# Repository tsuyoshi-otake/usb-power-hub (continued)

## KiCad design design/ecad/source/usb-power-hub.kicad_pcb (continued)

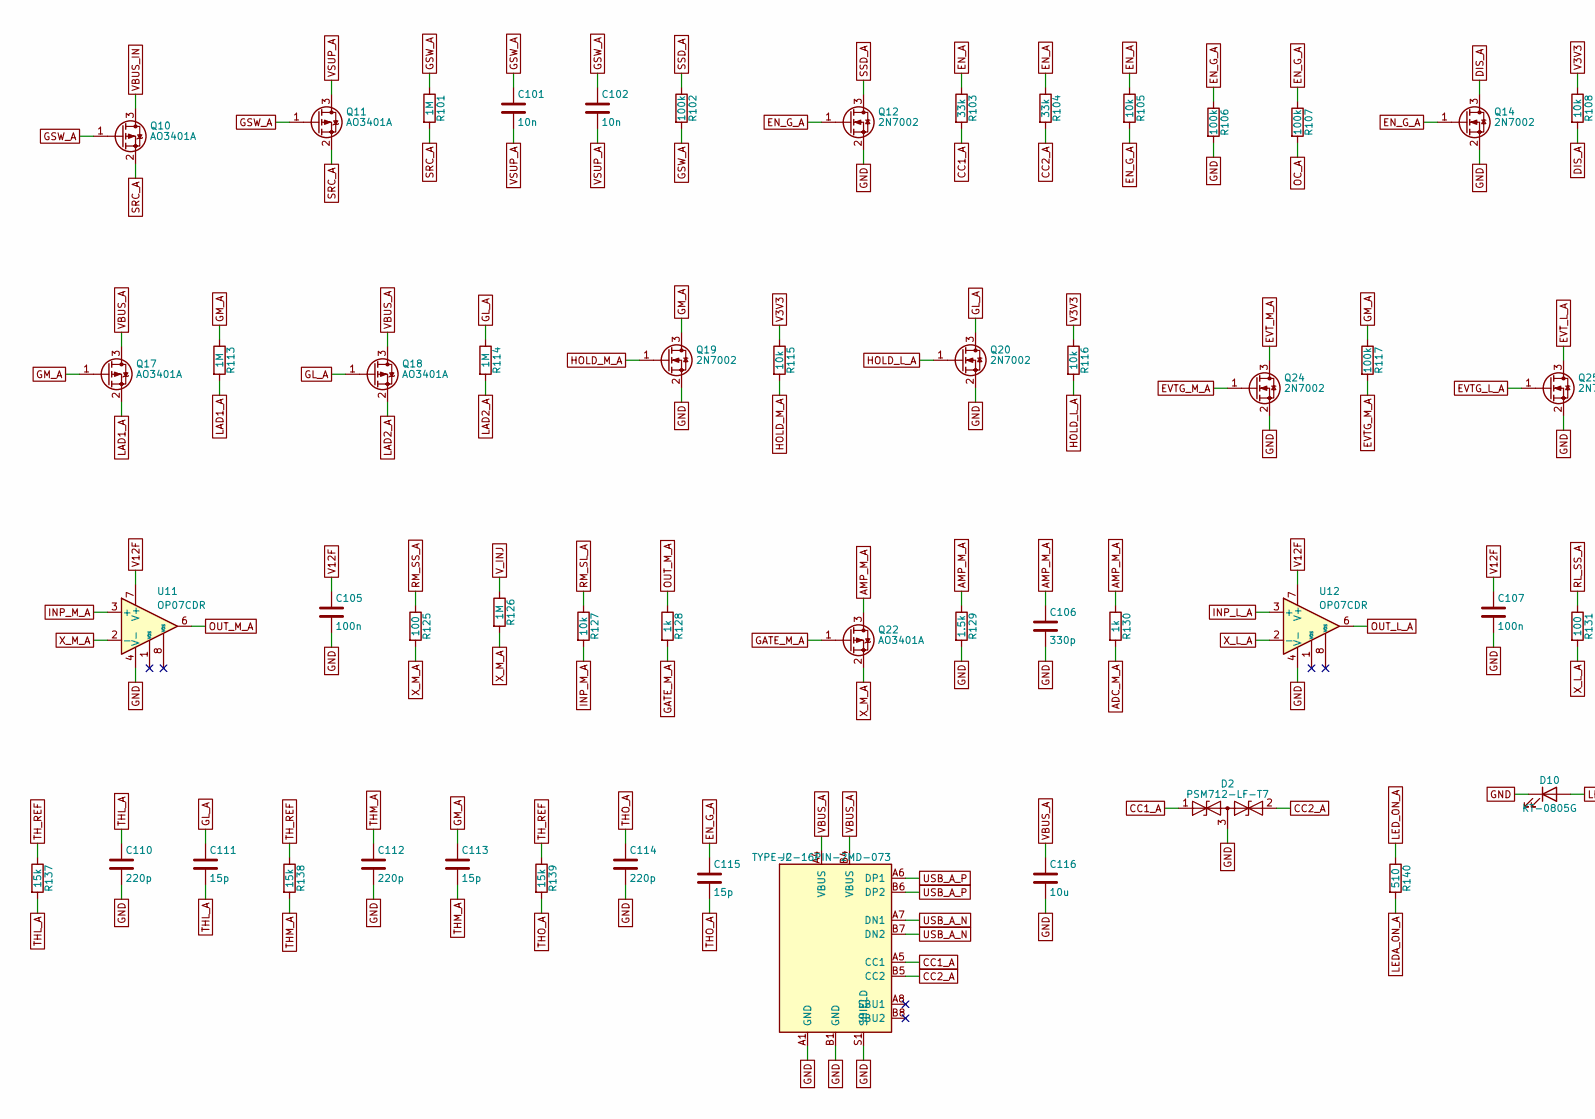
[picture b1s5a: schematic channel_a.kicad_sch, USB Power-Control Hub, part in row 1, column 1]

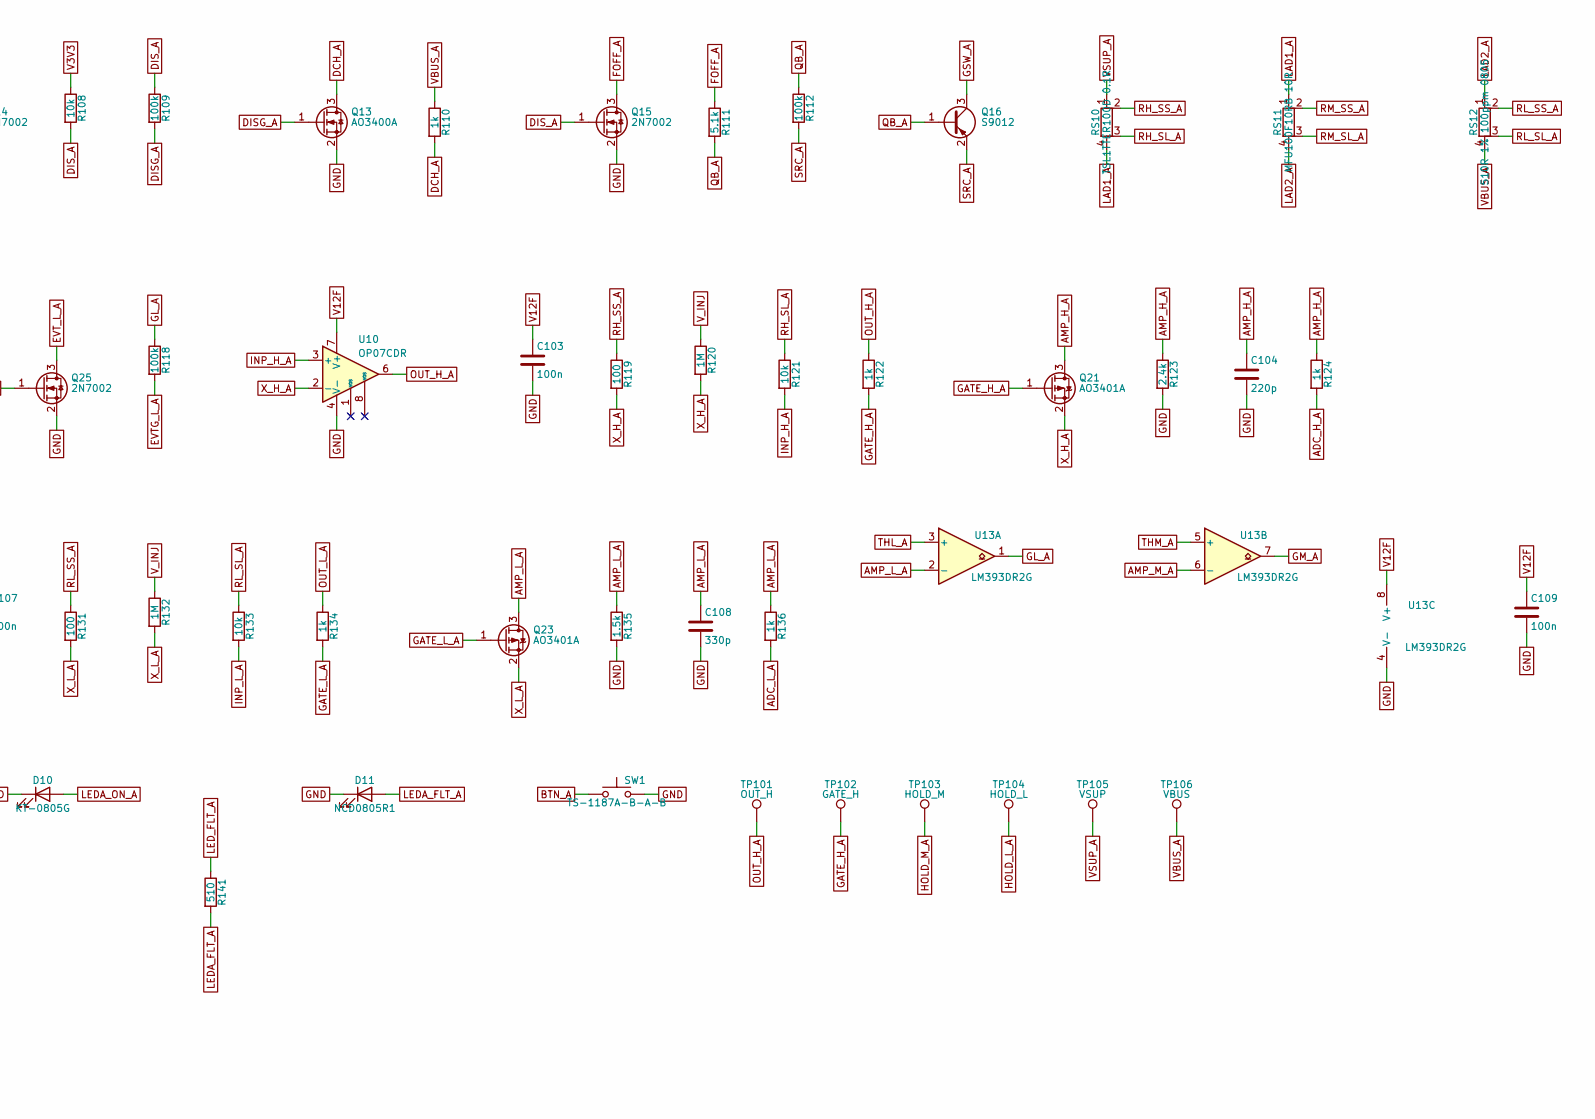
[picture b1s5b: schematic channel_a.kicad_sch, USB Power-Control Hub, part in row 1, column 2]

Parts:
C101, C102: 10n; C_0402_1005Metric; MPN CL05B103KB5NNNC; LCSC C15195
C103, C105, C107, C109: 100n; C_0402_1005Metric; MPN CL05B104KB54PNC; LCSC C307331
C104, C110, C112, C114: 220p; C_0402_1005Metric; MPN 0402B221K500NT; LCSC C1530
C106, C108: 330p; C_0603_1608Metric; MPN CL10C331JB8NNNC; LCSC C1664
C111, C113, C115: 15p; C_0402_1005Metric; MPN 0402CG150J500NT; LCSC C1548
C116: 10u; C_0805_2012Metric; MPN CL21A106KAYNNNE; LCSC C15850
D2: PSM712-LF-T7; SOT-23; MPN PSM712-LF-T7; LCSC C32677
D10: KT-0805G; LED_0805_2012Metric; MPN KT-0805G; LCSC C2297
D11: NCD0805R1; LED_0805_2012Metric; MPN NCD0805R1; LCSC C84256
J2: TYPE-C-16PIN-2MD-073; USB_C_Receptacle_SHOUHAN_TYPE-C-16PIN-2MD-073; MPN TYPE-C 16PIN 2MD(073); LCSC C2765186
Q10, Q11, Q17, Q18, Q21, Q22, Q23: AO3401A; SOT-23; MPN AO3401A; LCSC C15127
Q12, Q14, Q15, Q19, Q20, Q24, Q25: 2N7002; SOT-23; MPN 2N7002; LCSC C8545
Q13: AO3400A; SOT-23; MPN AO3400A; LCSC C20917
Q16: S9012; SOT-23; MPN S9012 (rank H, marking 2T1); LCSC C8543
R101, R113, R114, R120, R126, R132: 1M; R_0402_1005Metric; MPN 0402WGF1004TCE; LCSC C26083
R102, R106, R107, R109, R112, R117, R118: 100k; R_0402_1005Metric; MPN 0402WGF1003TCE; LCSC C25741
R103, R104: 33k; R_0402_1005Metric; MPN 0402WGF3302TCE; LCSC C25779
R105, R108, R115, R116, R121, R127, R133: 10k; R_0402_1005Metric; MPN 0402WGF1002TCE; LCSC C25744
R110, R122, R124, R128, R130, R134, R136: 1k; R_0402_1005Metric; MPN 0402WGF1001TCE; LCSC C11702
R111: 5.1k; R_0402_1005Metric; MPN 0402WGF5101TCE; LCSC C25905
R119, R125, R131: 100; R_0402_1005Metric; MPN 0402WGF1000TCE; LCSC C25076
R123: 2.4k; R_0603_1608Metric; MPN 0603WAF2401T5E; LCSC C22940
R129, R135: 1.5k; R_0402_1005Metric; MPN 0402WGF1501TCE; LCSC C25867
R137, R138, R139: 15k; R_0402_1005Metric; MPN 0402WGF1502TCE; LCSC C25756
R140, R141: 510; R_0805_2012Metric; MPN 0805W8F5100T5E; LCSC C17734
RS10: TSL1TTER100D 0.1R; R_Shunt_KOA_TSL1_6332Metric_Kelvin; MPN TSL1TTER100D
RS11: MFU100F10RB 10R; R_Shunt_Axial_MFU_L6.0mm_D2.3mm_P10.16mm_Kelvin; MPN MFU100F10RB
RS12: 510R 1% 100ppm 0805; R_Shunt_0805_2012Metric_Kelvin; LCSC C17734
SW1: TS-1187A-B-A-B; SW_Push_1P1T_XKB_TS-1187A; MPN TS-1187A-B-A-B; LCSC C318884
TP101: OUT_H; TestPoint_Pad_D1.0mm
TP102: GATE_H; TestPoint_Pad_D1.0mm
TP103: HOLD_M; TestPoint_Pad_D1.0mm
TP104: HOLD_L; TestPoint_Pad_D1.0mm
TP105: VSUP; TestPoint_Pad_D1.0mm
TP106: VBUS; TestPoint_Pad_D1.0mm
U10, U11, U12: OP07CDR; SOIC-8_3.9x4.9mm_P1.27mm; MPN OP07CDR; LCSC C7433
U13: LM393DR2G; SOIC-8_3.9x4.9mm_P1.27mm; MPN LM393DR2G; LCSC C7955

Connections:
ADC_H_A: R124.2; also elsewhere on the board
ADC_L_A: R136.2; also elsewhere on the board
ADC_M_A: R130.2; also elsewhere on the board
AMP_H_A: C104.1, Q21.3 (D), R123.1, R124.1; also elsewhere on the board
AMP_L_A: C108.1, Q23.3 (D), R135.1, R136.1, U13.2 (-)
AMP_M_A: C106.1, Q22.3 (D), R129.1, R130.1, U13.6 (-)
BTN_A: SW1.1; also elsewhere on the board
CC1_A: D2.1 (A1), J2.A5 (CC1), R103.2
CC2_A: D2.2 (A2), J2.B5 (CC2), R104.2
DCH_A: Q13.3 (D), R110.2
DISG_A: Q13.1 (G), R109.2
DIS_A: Q14.3 (D), Q15.1 (G), R108.2, R109.1
EN_A: R103.1, R104.1, R105.1; also elsewhere on the board
EN_G_A: C115.1, Q12.1 (G), Q14.1 (G), R105.2, R106.1, R107.1; also elsewhere on the board
EVTG_L_A: Q25.1 (G), R118.2
EVTG_M_A: Q24.1 (G), R117.2
EVT_L_A: Q25.3 (D); also elsewhere on the board
EVT_M_A: Q24.3 (D); also elsewhere on the board
FOFF_A: Q15.3 (D), R111.1
GATE_H_A: Q21.1 (G), R122.2, TP102.1
GATE_L_A: Q23.1 (G), R134.2
GATE_M_A: Q22.1 (G), R128.2
GL_A: C111.1, Q18.1 (G), Q20.3 (D), R114.1, R118.1, U13.1
GM_A: C113.1, Q17.1 (G), Q19.3 (D), R113.1, R117.1, U13.7
GND: C103.2, C104.2, C105.2, C106.2, C107.2, C108.2, C109.2, C110.2, C112.2, C114.2, C116.2, D2.3 (common), D10.1 (K), D11.1 (K), J2.A1 (GND), J2.B1 (GND), J2.S1 (SHIELD), Q12.2 (S), Q13.2 (S), Q14.2 (S), Q15.2 (S), Q19.2 (S), Q20.2 (S), Q24.2 (S), Q25.2 (S), R106.2, R123.2, R129.2, R135.2, SW1.2, U10.4 (V-), U11.4 (V-), U12.4 (V-), U13.4 (V-); also elsewhere on the board
GSW_A: C101.1, C102.1, Q10.1 (G), Q11.1 (G), Q16.3 (C), R101.1, R102.2
HOLD_L_A: Q20.1 (G), R116.2, TP104.1; also elsewhere on the board
HOLD_M_A: Q19.1 (G), R115.2, TP103.1; also elsewhere on the board
INP_H_A: R121.2, U10.3 (+)
INP_L_A: R133.2, U12.3 (+)
INP_M_A: R127.2, U11.3 (+)
LAD1_A: Q17.2 (S), R113.2, RS10.4, RS11.1
LAD2_A: Q18.2 (S), R114.2, RS11.4, RS12.1
LEDA_FLT_A: D11.2 (A), R141.2
LEDA_ON_A: D10.2 (A), R140.2
LED_FLT_A: R141.1; also elsewhere on the board
LED_ON_A: R140.1; also elsewhere on the board
OC_A: R107.2; also elsewhere on the board
OUT_H_A: R122.1, TP101.1, U10.6
OUT_L_A: R134.1, U12.6
OUT_M_A: R128.1, U11.6
QB_A: Q16.1 (B), R111.2, R112.1
RH_SL_A: R121.1, RS10.3
RH_SS_A: R119.1, RS10.2
RL_SL_A: R133.1, RS12.3
RL_SS_A: R131.1, RS12.2
RM_SL_A: R127.1, RS11.3
RM_SS_A: R125.1, RS11.2
SRC_A: Q10.2 (S), Q11.2 (S), Q16.2 (E), R101.2, R112.2
SSD_A: Q12.3 (D), R102.1
THL_A: C110.1, C111.2, R137.2, U13.3 (+)
THM_A: C112.1, C113.2, R138.2, U13.5 (+)
THO_A: C114.1, C115.2, R139.2; also elsewhere on the board
TH_REF: R137.1, R138.1, R139.1; also elsewhere on the board
USB_A_N: J2.A7 (DN1), J2.B7 (DN2); also elsewhere on the board
USB_A_P: J2.A6 (DP1), J2.B6 (DP2); also elsewhere on the board
V3V3: R108.1, R115.1, R116.1; also elsewhere on the board
V12F: C103.1, C105.1, C107.1, C109.1, U10.7 (V+), U11.7 (V+), U12.7 (V+), U13.8 (V+); also elsewhere on the board
VBUS_A: C116.1, J2.A4 (VBUS), J2.B4 (VBUS), Q17.3 (D), Q18.3 (D), R110.1, RS12.4, TP106.1
VBUS_IN: Q10.3 (D); also elsewhere on the board
VSUP_A: C101.2, C102.2, Q11.3 (D), RS10.1, TP105.1
V_INJ: R120.1, R126.1, R132.1; also elsewhere on the board
X_H_A: Q21.2 (S), R119.2, R120.2, U10.2 (-)
X_L_A: Q23.2 (S), R131.2, R132.2, U12.2 (-)
X_M_A: Q22.2 (S), R125.2, R126.2, U11.2 (-)

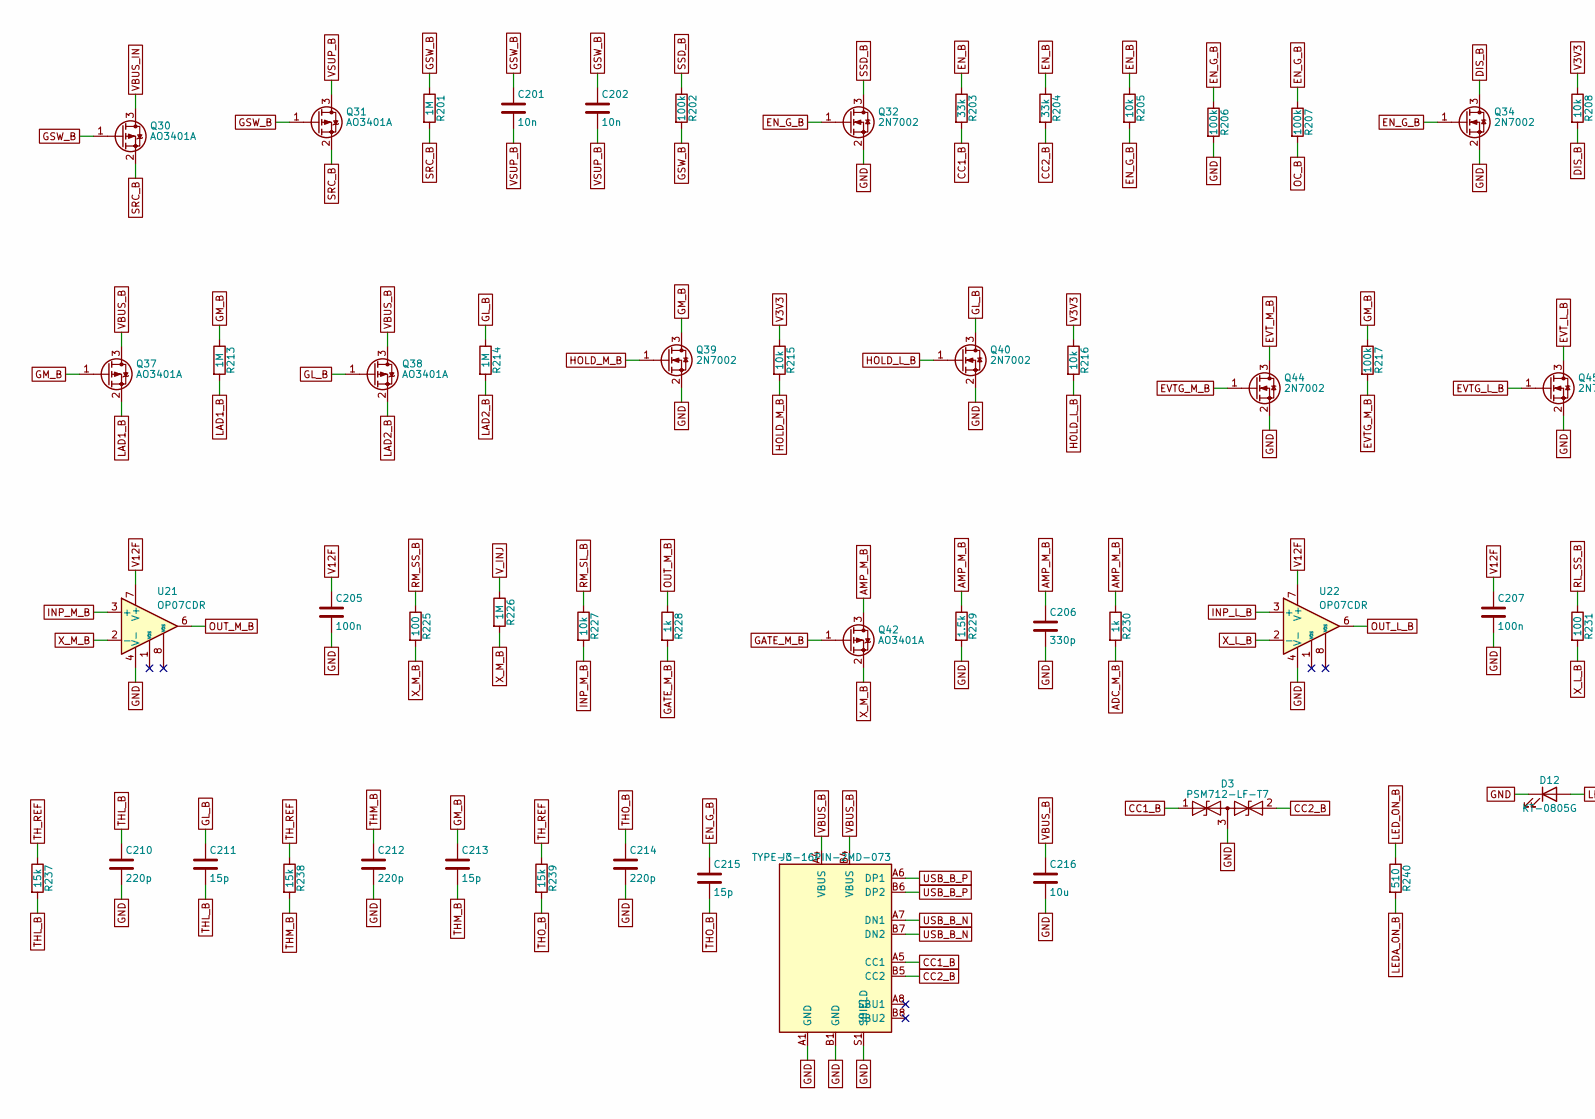
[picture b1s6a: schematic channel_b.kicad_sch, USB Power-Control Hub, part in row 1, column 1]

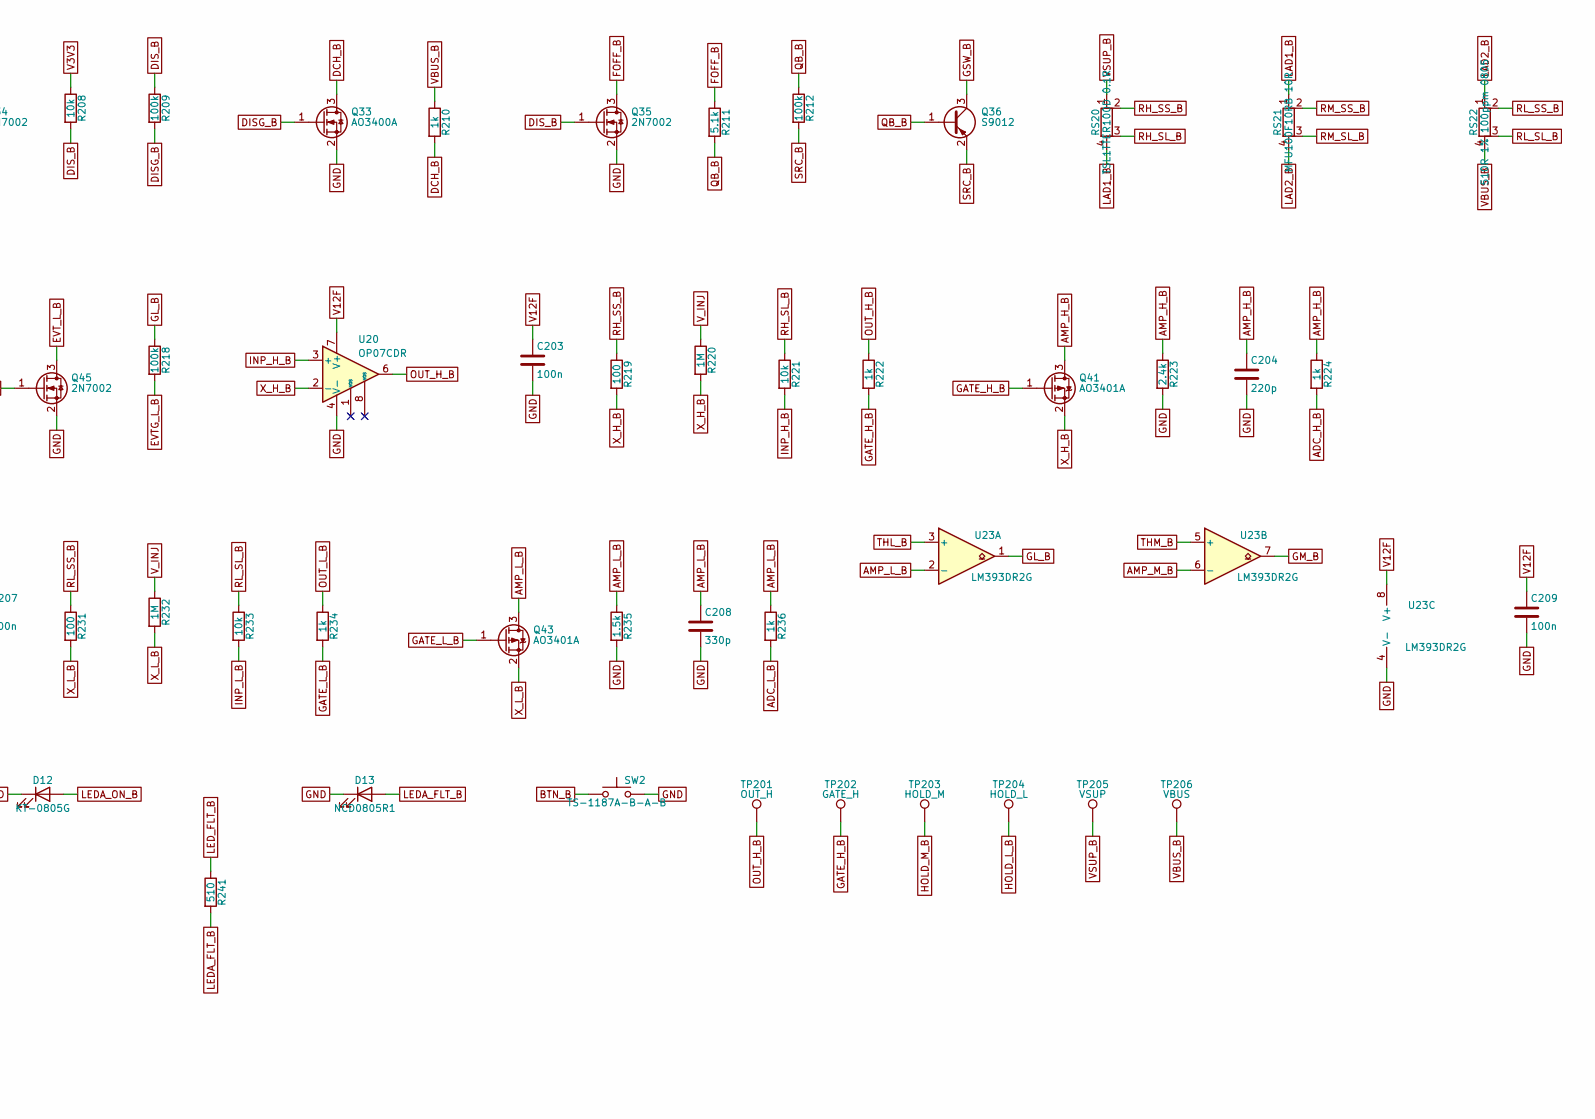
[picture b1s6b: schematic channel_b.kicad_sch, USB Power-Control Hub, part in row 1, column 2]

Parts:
C201, C202: 10n; C_0402_1005Metric; MPN CL05B103KB5NNNC; LCSC C15195
C203, C205, C207, C209: 100n; C_0402_1005Metric; MPN CL05B104KB54PNC; LCSC C307331
C204, C210, C212, C214: 220p; C_0402_1005Metric; MPN 0402B221K500NT; LCSC C1530
C206, C208: 330p; C_0603_1608Metric; MPN CL10C331JB8NNNC; LCSC C1664
C211, C213, C215: 15p; C_0402_1005Metric; MPN 0402CG150J500NT; LCSC C1548
C216: 10u; C_0805_2012Metric; MPN CL21A106KAYNNNE; LCSC C15850
D3: PSM712-LF-T7; SOT-23; MPN PSM712-LF-T7; LCSC C32677
D12: KT-0805G; LED_0805_2012Metric; MPN KT-0805G; LCSC C2297
D13: NCD0805R1; LED_0805_2012Metric; MPN NCD0805R1; LCSC C84256
J3: TYPE-C-16PIN-2MD-073; USB_C_Receptacle_SHOUHAN_TYPE-C-16PIN-2MD-073; MPN TYPE-C 16PIN 2MD(073); LCSC C2765186
Q30, Q31, Q37, Q38, Q41, Q42, Q43: AO3401A; SOT-23; MPN AO3401A; LCSC C15127
Q32, Q34, Q35, Q39, Q40, Q44, Q45: 2N7002; SOT-23; MPN 2N7002; LCSC C8545
Q33: AO3400A; SOT-23; MPN AO3400A; LCSC C20917
Q36: S9012; SOT-23; MPN S9012 (rank H, marking 2T1); LCSC C8543
R201, R213, R214, R220, R226, R232: 1M; R_0402_1005Metric; MPN 0402WGF1004TCE; LCSC C26083
R202, R206, R207, R209, R212, R217, R218: 100k; R_0402_1005Metric; MPN 0402WGF1003TCE; LCSC C25741
R203, R204: 33k; R_0402_1005Metric; MPN 0402WGF3302TCE; LCSC C25779
R205, R208, R215, R216, R221, R227, R233: 10k; R_0402_1005Metric; MPN 0402WGF1002TCE; LCSC C25744
R210, R222, R224, R228, R230, R234, R236: 1k; R_0402_1005Metric; MPN 0402WGF1001TCE; LCSC C11702
R211: 5.1k; R_0402_1005Metric; MPN 0402WGF5101TCE; LCSC C25905
R219, R225, R231: 100; R_0402_1005Metric; MPN 0402WGF1000TCE; LCSC C25076
R223: 2.4k; R_0603_1608Metric; MPN 0603WAF2401T5E; LCSC C22940
R229, R235: 1.5k; R_0402_1005Metric; MPN 0402WGF1501TCE; LCSC C25867
R237, R238, R239: 15k; R_0402_1005Metric; MPN 0402WGF1502TCE; LCSC C25756
R240, R241: 510; R_0805_2012Metric; MPN 0805W8F5100T5E; LCSC C17734
RS20: TSL1TTER100D 0.1R; R_Shunt_KOA_TSL1_6332Metric_Kelvin; MPN TSL1TTER100D
RS21: MFU100F10RB 10R; R_Shunt_Axial_MFU_L6.0mm_D2.3mm_P10.16mm_Kelvin; MPN MFU100F10RB
RS22: 510R 1% 100ppm 0805; R_Shunt_0805_2012Metric_Kelvin; LCSC C17734
SW2: TS-1187A-B-A-B; SW_Push_1P1T_XKB_TS-1187A; MPN TS-1187A-B-A-B; LCSC C318884
TP201: OUT_H; TestPoint_Pad_D1.0mm
TP202: GATE_H; TestPoint_Pad_D1.0mm
TP203: HOLD_M; TestPoint_Pad_D1.0mm
TP204: HOLD_L; TestPoint_Pad_D1.0mm
TP205: VSUP; TestPoint_Pad_D1.0mm
TP206: VBUS; TestPoint_Pad_D1.0mm
U20, U21, U22: OP07CDR; SOIC-8_3.9x4.9mm_P1.27mm; MPN OP07CDR; LCSC C7433
U23: LM393DR2G; SOIC-8_3.9x4.9mm_P1.27mm; MPN LM393DR2G; LCSC C7955

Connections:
ADC_H_B: R224.2; also elsewhere on the board
ADC_L_B: R236.2; also elsewhere on the board
ADC_M_B: R230.2; also elsewhere on the board
AMP_H_B: C204.1, Q41.3 (D), R223.1, R224.1; also elsewhere on the board
AMP_L_B: C208.1, Q43.3 (D), R235.1, R236.1, U23.2 (-)
AMP_M_B: C206.1, Q42.3 (D), R229.1, R230.1, U23.6 (-)
BTN_B: SW2.1; also elsewhere on the board
CC1_B: D3.1 (A1), J3.A5 (CC1), R203.2
CC2_B: D3.2 (A2), J3.B5 (CC2), R204.2
DCH_B: Q33.3 (D), R210.2
DISG_B: Q33.1 (G), R209.2
DIS_B: Q34.3 (D), Q35.1 (G), R208.2, R209.1
EN_B: R203.1, R204.1, R205.1; also elsewhere on the board
EN_G_B: C215.1, Q32.1 (G), Q34.1 (G), R205.2, R206.1, R207.1; also elsewhere on the board
EVTG_L_B: Q45.1 (G), R218.2
EVTG_M_B: Q44.1 (G), R217.2
EVT_L_B: Q45.3 (D); also elsewhere on the board
EVT_M_B: Q44.3 (D); also elsewhere on the board
FOFF_B: Q35.3 (D), R211.1
GATE_H_B: Q41.1 (G), R222.2, TP202.1
GATE_L_B: Q43.1 (G), R234.2
GATE_M_B: Q42.1 (G), R228.2
GL_B: C211.1, Q38.1 (G), Q40.3 (D), R214.1, R218.1, U23.1
GM_B: C213.1, Q37.1 (G), Q39.3 (D), R213.1, R217.1, U23.7
GND: C203.2, C204.2, C205.2, C206.2, C207.2, C208.2, C209.2, C210.2, C212.2, C214.2, C216.2, D3.3 (common), D12.1 (K), D13.1 (K), J3.A1 (GND), J3.B1 (GND), J3.S1 (SHIELD), Q32.2 (S), Q33.2 (S), Q34.2 (S), Q35.2 (S), Q39.2 (S), Q40.2 (S), Q44.2 (S), Q45.2 (S), R206.2, R223.2, R229.2, R235.2, SW2.2, U20.4 (V-), U21.4 (V-), U22.4 (V-), U23.4 (V-); also elsewhere on the board
GSW_B: C201.1, C202.1, Q30.1 (G), Q31.1 (G), Q36.3 (C), R201.1, R202.2
HOLD_L_B: Q40.1 (G), R216.2, TP204.1; also elsewhere on the board
HOLD_M_B: Q39.1 (G), R215.2, TP203.1; also elsewhere on the board
INP_H_B: R221.2, U20.3 (+)
INP_L_B: R233.2, U22.3 (+)
INP_M_B: R227.2, U21.3 (+)
LAD1_B: Q37.2 (S), R213.2, RS20.4, RS21.1
LAD2_B: Q38.2 (S), R214.2, RS21.4, RS22.1
LEDA_FLT_B: D13.2 (A), R241.2
LEDA_ON_B: D12.2 (A), R240.2
LED_FLT_B: R241.1; also elsewhere on the board
LED_ON_B: R240.1; also elsewhere on the board
OC_B: R207.2; also elsewhere on the board
OUT_H_B: R222.1, TP201.1, U20.6
OUT_L_B: R234.1, U22.6
OUT_M_B: R228.1, U21.6
QB_B: Q36.1 (B), R211.2, R212.1
RH_SL_B: R221.1, RS20.3
RH_SS_B: R219.1, RS20.2
RL_SL_B: R233.1, RS22.3
RL_SS_B: R231.1, RS22.2
RM_SL_B: R227.1, RS21.3
RM_SS_B: R225.1, RS21.2
SRC_B: Q30.2 (S), Q31.2 (S), Q36.2 (E), R201.2, R212.2
SSD_B: Q32.3 (D), R202.1
THL_B: C210.1, C211.2, R237.2, U23.3 (+)
THM_B: C212.1, C213.2, R238.2, U23.5 (+)
THO_B: C214.1, C215.2, R239.2; also elsewhere on the board
TH_REF: R237.1, R238.1, R239.1; also elsewhere on the board
USB_B_N: J3.A7 (DN1), J3.B7 (DN2); also elsewhere on the board
USB_B_P: J3.A6 (DP1), J3.B6 (DP2); also elsewhere on the board
V3V3: R208.1, R215.1, R216.1; also elsewhere on the board
V12F: C203.1, C205.1, C207.1, C209.1, U20.7 (V+), U21.7 (V+), U22.7 (V+), U23.8 (V+); also elsewhere on the board
VBUS_B: C216.1, J3.A4 (VBUS), J3.B4 (VBUS), Q37.3 (D), Q38.3 (D), R210.1, RS22.4, TP206.1
VBUS_IN: Q30.3 (D); also elsewhere on the board
VSUP_B: C201.2, C202.2, Q31.3 (D), RS20.1, TP205.1
V_INJ: R220.1, R226.1, R232.1; also elsewhere on the board
X_H_B: Q41.2 (S), R219.2, R220.2, U20.2 (-)
X_L_B: Q43.2 (S), R231.2, R232.2, U22.2 (-)
X_M_B: Q42.2 (S), R225.2, R226.2, U21.2 (-)

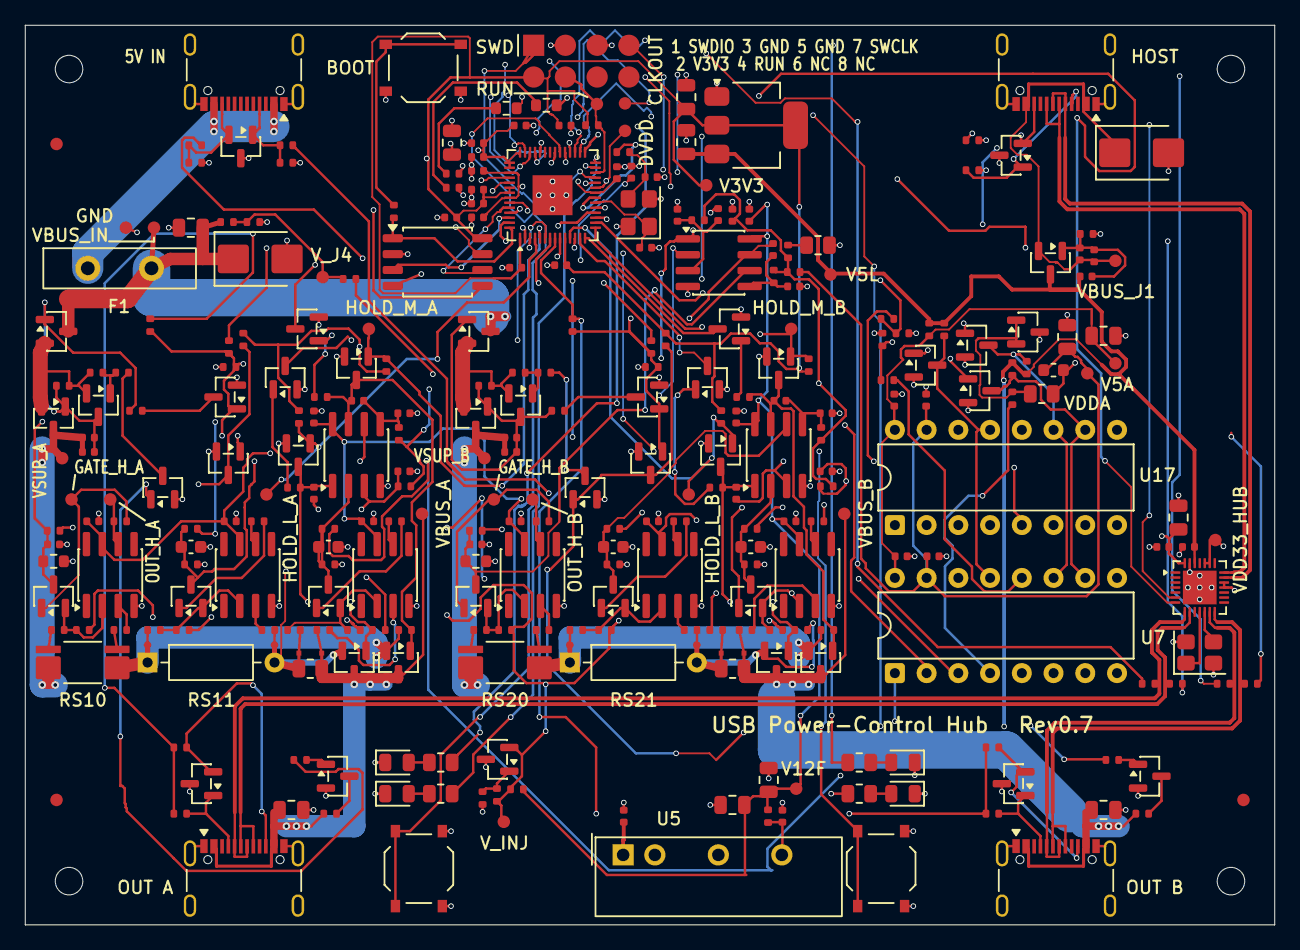
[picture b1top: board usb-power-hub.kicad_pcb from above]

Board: 4 copper layers, 100.0 x 72.0 mm, 304 parts (0 on the bottom side), 183 nets.

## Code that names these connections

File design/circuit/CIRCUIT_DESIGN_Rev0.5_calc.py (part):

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for j4, v5 in ((5.25, 4.5), (5.5, 4.75), (5.5, 4.5)):
    for r in ("LOW", "HIGH"):
        node = j4 * ROUT[r] / (ROUT[r] + R1 + RDS)
        print(f"overrange J4={j4} V, V5A={v5} V: {r} node max {node:.2f} V vs pin abs max {v5+0.6:.2f} V"
              f" -> margin {v5+0.6-node:+.2f} V")
node_hi = 5.25 * ROUT["HIGH"] / (ROUT["HIGH"] + R1 + RDS)
print(f"(with V_DD = 3.3 V instead, the HIGH node at J4 5.25 V would drive"
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RAILS = {"USB_VDD": (3.135, 3.63), "IOVDD": (1.62, 3.63), "VREG_VIN": (1.62, 3.63),
         "ADC_AVDD": (1.62, 3.63), "W25Q128JV VCC": (2.7, 3.6)}   # RP2040 DS Table 634; Winbond
for pin, (lo, hi) in RAILS.items():
    print(f"{pin} {lo}-{hi} V on V3V3 {V3V3_MIN}-{V3V3_MAX} V: margin {V3V3_MIN-lo:+.3f} V low,"
          f" {hi-V3V3_MAX:+.3f} V high")
I_DVDD = {"BOOTSEL active": 14.7, "Popcorn demo": 16.6}   # DS Table 637, maximum column, mA
for case, i in I_DVDD.items():
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      f" typical I_OL 0.1 nA -> {-(0.1e-9+IDSS_2N7002)*1e6*1e3:.0f} mV (checked by V-MEAS-01)")

print("\n== Sec. 3.1 / Sec. 7.1 J1 soft start (D35, OI-32): Q53 AO3401A between VBUS_J1 and V5L")
# Q53: source VBUS_J1 (J1 pin 1, D5), drain V5L. R34 33 k gate -> GND turns it on; C35 100 nF
# gate -> drain (V5L) is the Miller capacitor that sets V5L's ramp; C36 + C37, 2 x 1 uF gate ->
# source, hold the gate at the source when VBUS_J1 steps up at plug-in. No gate-source resistor:
# the gate ends at GND, V_GS = -V_J1.
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          f" at J1 {I_J1_MAX*1e3:.0f} mA the drop is <= {I_J1_MAX*r25*1e3:.0f} / {I_J1_MAX*r25*1.23*1e3:.0f} mV,"
          f" {I_J1_MAX**2*r25*1.23*1e3:.1f} mW")
drop_hi = I_J1_MAX * rds_j(VJ1[0]) * 1.23
print(f"V5L >= {V5L_MIN} V (U6 V5 and MAU104 minimum) now needs J1 >= {V5L_MIN + drop_hi:.3f} V at the module pin")

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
